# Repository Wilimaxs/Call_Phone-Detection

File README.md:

# 📞 Callphone Detection

Deteksi sederhana untuk mengetahui apakah seseorang sedang menggunakan handphone untuk menelepon. Proyek ini dirancang sebagai sistem ringan dengan komponen minimal untuk pengujian atau pembelajaran dasar sistem deteksi aktivitas. dapat dikembangkan lebih lanjut untuk mendeteksi penggunaan handphone dalam ruangan ujian

---

## 🖼️ Mockup

| Schematic | Board |
|----------|--------|
|  |  |

---

## 🎯 Fitur

- Deteksi handphone yang sedang digunakan untuk menelepon
- Output sederhana (LED dan buzzer)
- Cocok untuk prototipe awal dalam pembuatan pendeteksi kecurangan dalam ujian

---

## 🧰 Komponen

- Sensor elektromagnetik / RF detector / sensor khusus lain
- LED / Buzzer (opsional sebagai output indikator)
- Kabel jumper, breadboard, dan catu daya

---

## ⚙️ Cara Kerja Singkat

Sensor akan mendeteksi sinyal RF atau gelombang elektromagnetik yang khas saat handphone melakukan panggilan. Ketika sinyal tersebut terdeteksi, mikrokontroler akan memberikan output, menyalakan LED atau mengirim sinyal digital.

---

## 🚀 Instalasi & Penggunaan

1. Rakit komponen sesuai skematik
3. Uji sistem dengan melakukan panggilan telepon dekat sensor ataupun menjauhinya

---

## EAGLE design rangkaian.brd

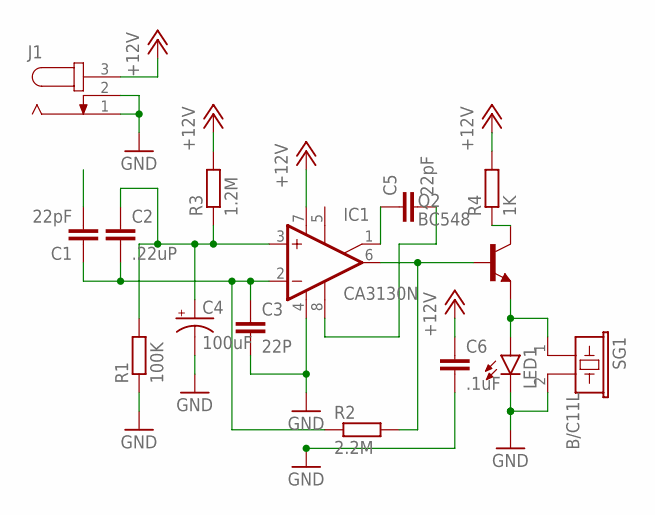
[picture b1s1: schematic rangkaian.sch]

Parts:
C1, C5: 22pF; C025-025X050
C2: .22uP; C025-025X050
C3: 22P; C025-025X050
C4: 100uF; E3,5-8
C6: .1uF; C025-025X050
IC1: CA3130N; DIL08
J1: JACK-PLUG0; SPC4077
LED1: LED5MM
Q2: BC548; TO92-EBC
R1: 100K; 0204/7
R2: 2.2M; 0204/7
R3: 1.2M; 0204/7
R4: 1K; 0204/7
SG1: B/C11L

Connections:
+12V: C6.1, IC1.7 (V+), J1.3, R3.2, R4.2
GND: C3.2, C4.-, C6.2, IC1.4 (V-), J1.1, J1.2, LED1.K (C), R1.1, SG1.2
unnamed: C1.1, C2.2, C3.1, IC1.2 (-IN), R2.1
unnamed: C2.1, C4.+, IC1.3 (+IN), R1.2, R3.1
unnamed: IC1.6 (OUT), Q2.B, R2.2
unnamed: LED1.A, Q2.E, SG1.1
unnamed: Q2.C, R4.1
unnamed: C5.2, IC1.8 (CMP)
unnamed: C5.1, IC1.1 (ON/CMP)

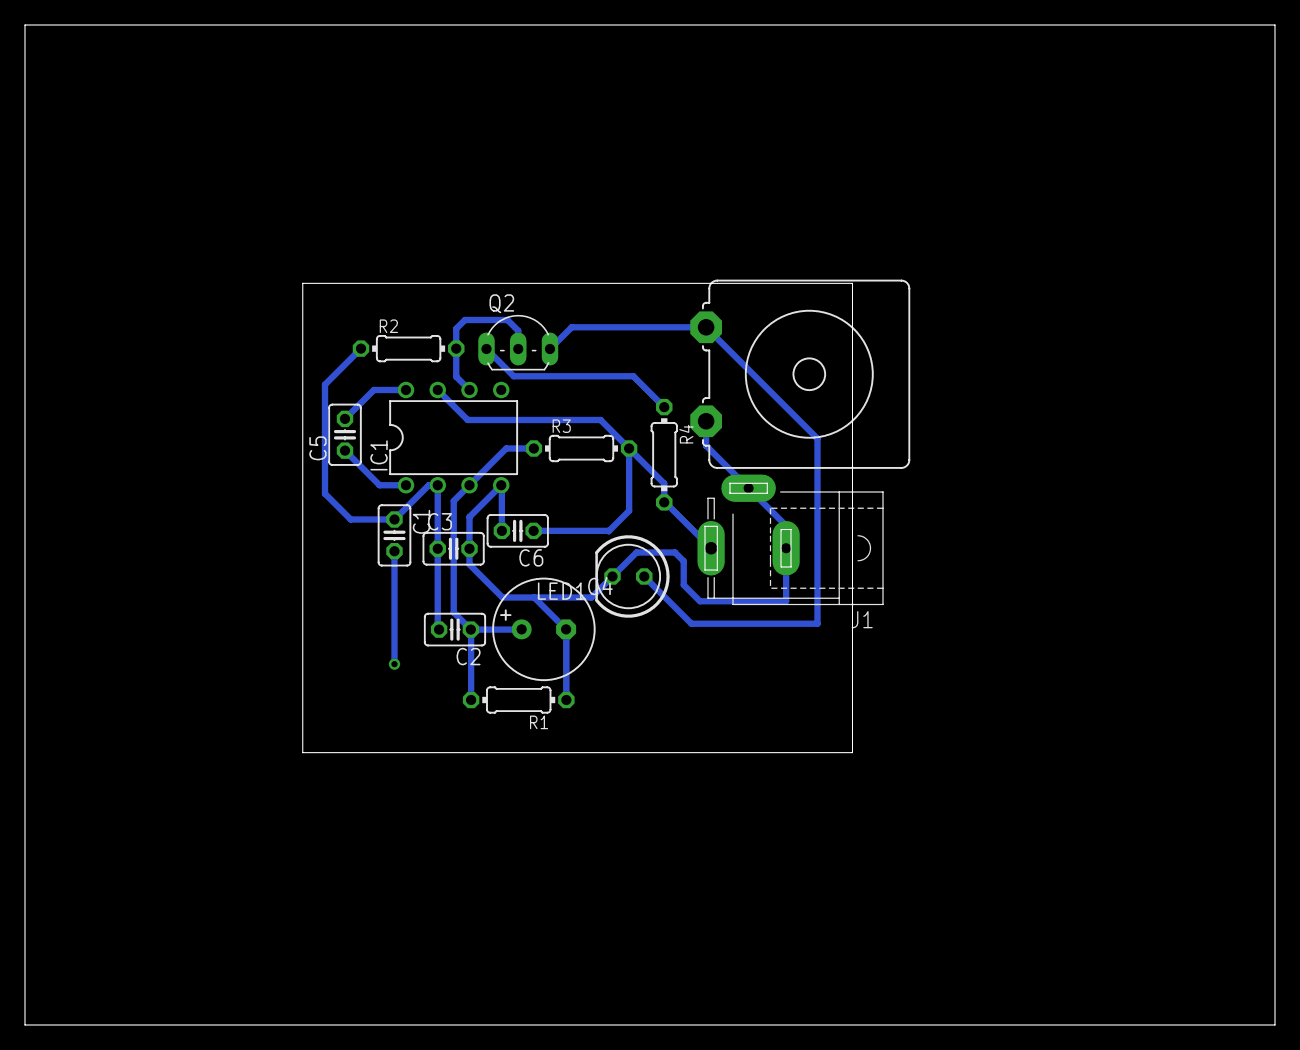
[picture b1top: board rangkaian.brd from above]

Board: 2 copper layers, 99.9 x 79.9 mm, 15 parts (0 on the bottom side), 9 nets.

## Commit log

2025-04-08 Rename Screenshot 2025-04-08 144711.png to sch
